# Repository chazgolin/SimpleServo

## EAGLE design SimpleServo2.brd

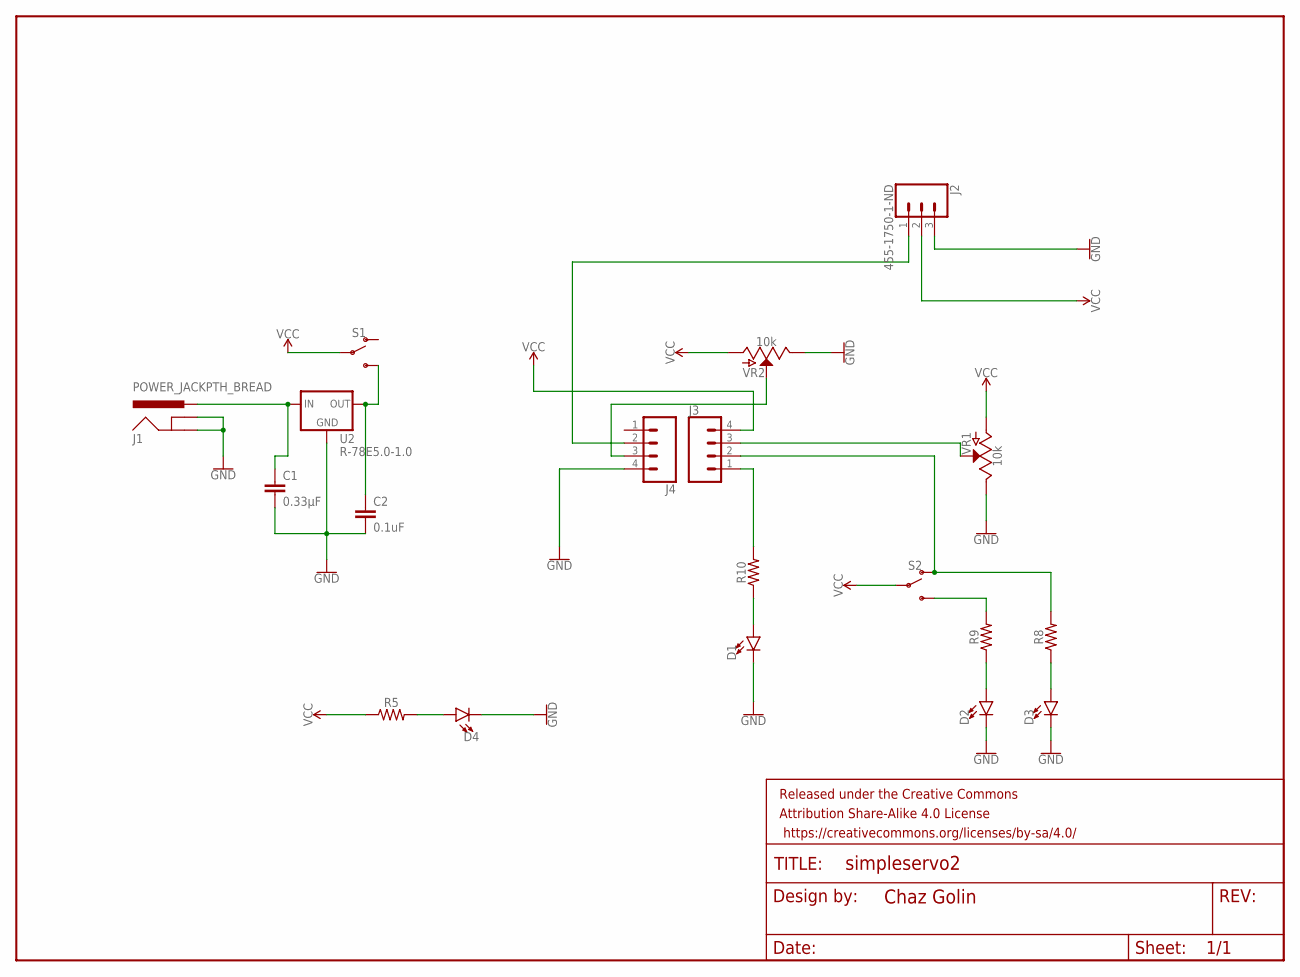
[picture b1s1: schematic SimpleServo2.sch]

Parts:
C1: 0.33µF; 0805
C2: 0.1uF; 0402
D1, D2, D3, D4: LED3MM; LED_3MM
FRAME1: FRAME-LETTER; CREATIVE_COMMONS
J1: POWER_JACKPTH_BREAD; POWER_JACK_PTH_BREAD
J2: 455-1750-1-ND; 1X03
J3, J4: CONN_041X04_NO_SILK; 1X04_NO_SILK
R5, R8, R9, R10: AXIAL-0.3
S1, S2: SWITCH-SPDT-PTH-11.6X4.0MM; SWITCH_SPDT_PTH_11.6X4.0MM
U2: R-78E5.0-1.0; DC-DC_CONVERTER_78XX
VR1, VR2: 10k; POT-PTH-ALPS

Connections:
GND: C1.2, C2.2, D1.K (C), D2.K (C), D3.K (C), D4.K (C), J1.GND, J1.GNDBREAK, J2.3, J4.4, U2.GND, VR1.P$1 (E), VR2.P$1 (E)
unnamed: C1.1, J1.PWR, U2.VIN (IN)
unnamed: C2.1, S1.3 (S), U2.VOUT (OUT)
unnamed: J3.1, R10.P$2 (2)
unnamed: J3.3, VR1.P$2 (S)
unnamed: D1.A, R10.P$1 (1)
unnamed: J4.3, VR2.P$2 (S)
unnamed: J3.2, R8.P$2 (2), S2.1 (O)
unnamed: R9.P$2 (2), S2.3 (S)
unnamed: D2.A, R9.P$1 (1)
unnamed: D3.A, R8.P$1 (1)
unnamed: J2.1, J4.2
unnamed: D4.A, R5.P$2 (2)
VCC: J2.2, J3.4, R5.P$1 (1), S1.2, S2.2, VR1.P$3 (A), VR2.P$3 (A)

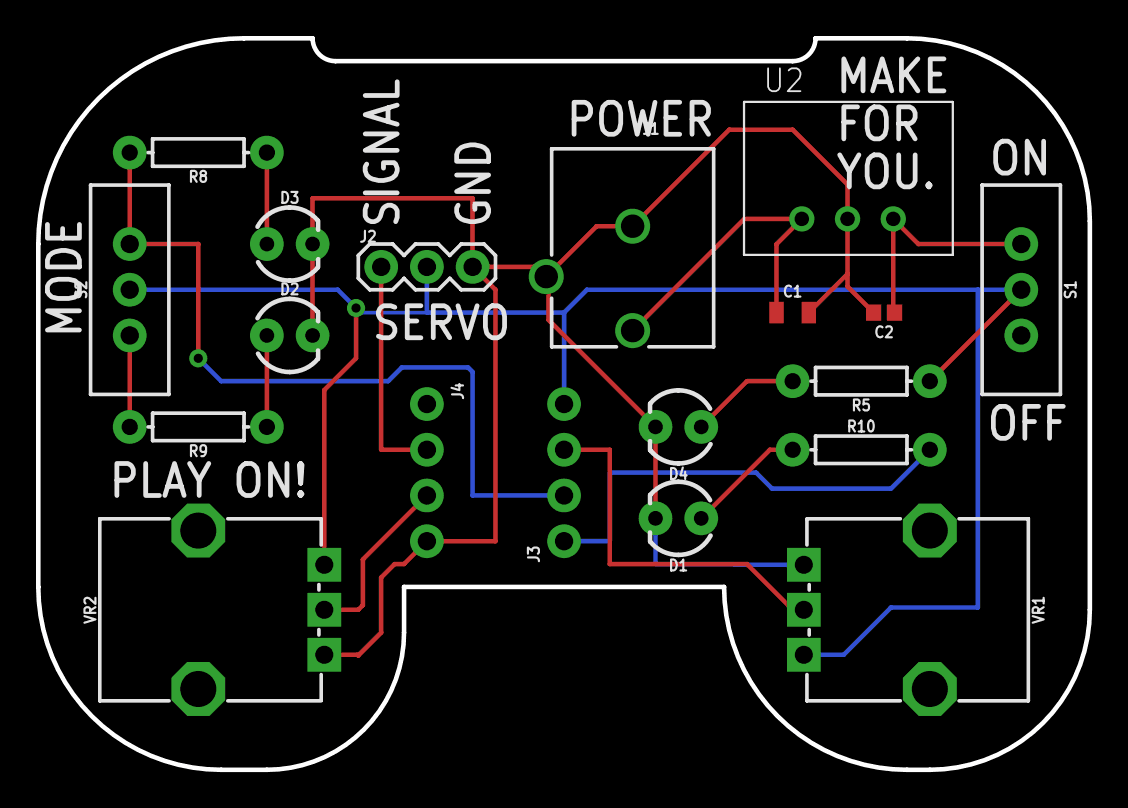
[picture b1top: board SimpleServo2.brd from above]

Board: 2 copper layers, 58.4 x 40.6 mm, 20 parts (0 on the bottom side), 14 nets.

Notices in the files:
parts and their libraries:
SparkFun-Capacitors: Licensing: Creative Commons ShareAlike 4.0 International - https://creativecommons.org/licenses/by-sa/4.0
SparkFun-Aesthetics: Released under the Creative Commons Attribution Share-Alike 4.0 License
SparkFun-Aesthetics: https://creativecommons.org/licenses/by-sa/4.0
